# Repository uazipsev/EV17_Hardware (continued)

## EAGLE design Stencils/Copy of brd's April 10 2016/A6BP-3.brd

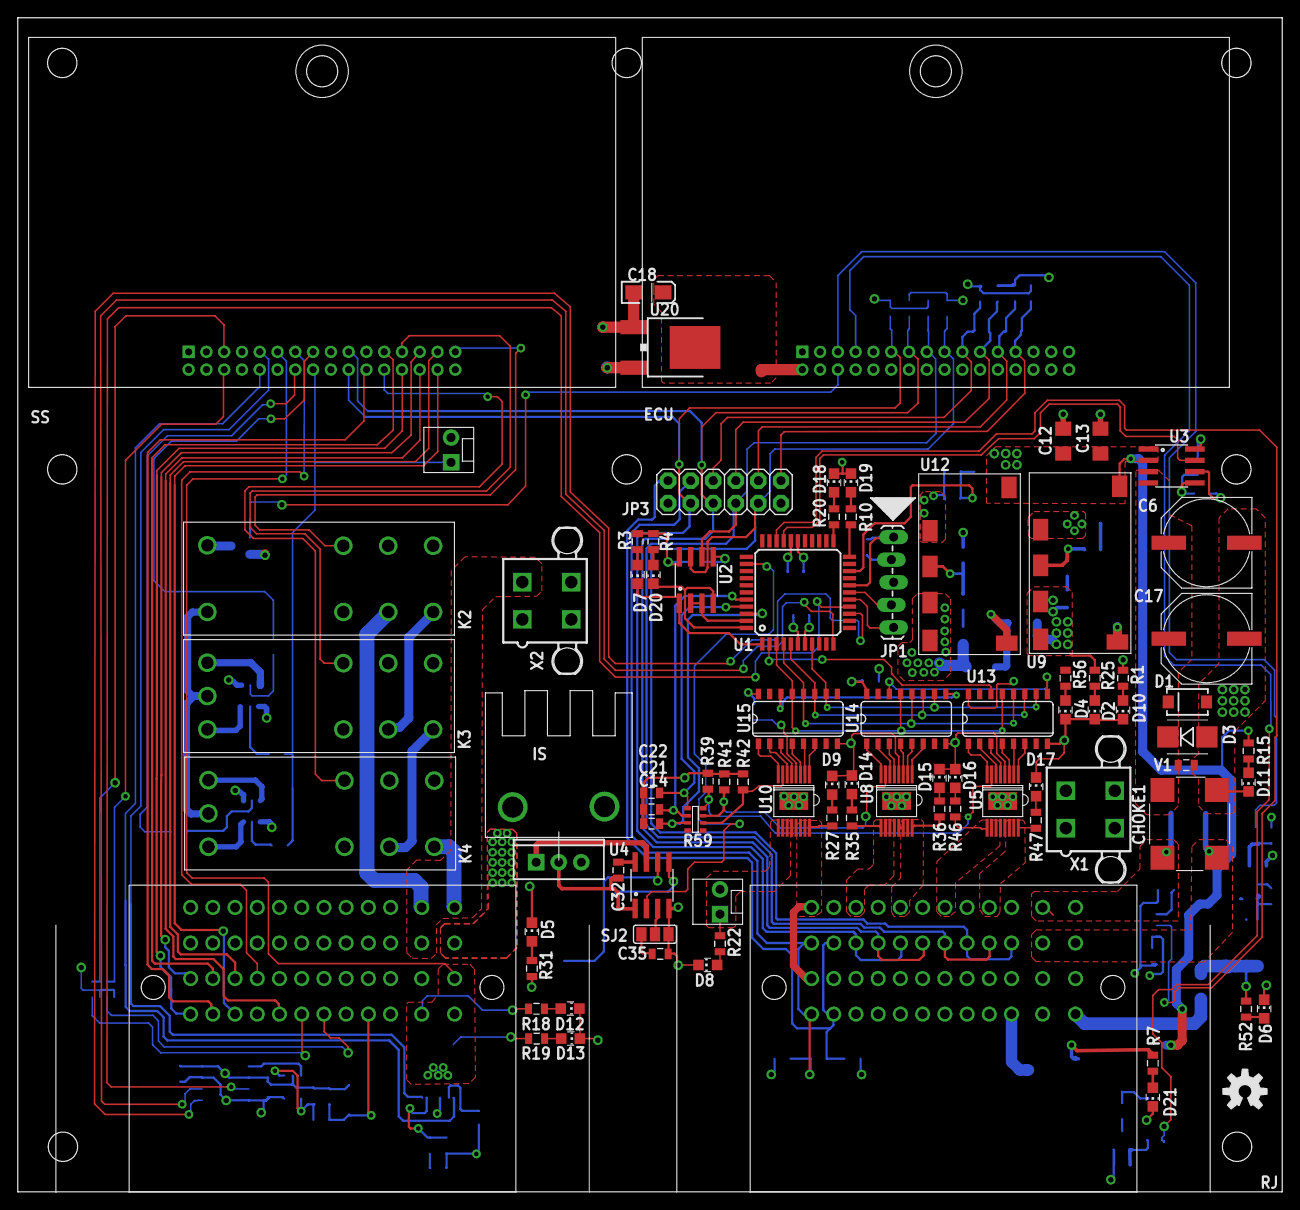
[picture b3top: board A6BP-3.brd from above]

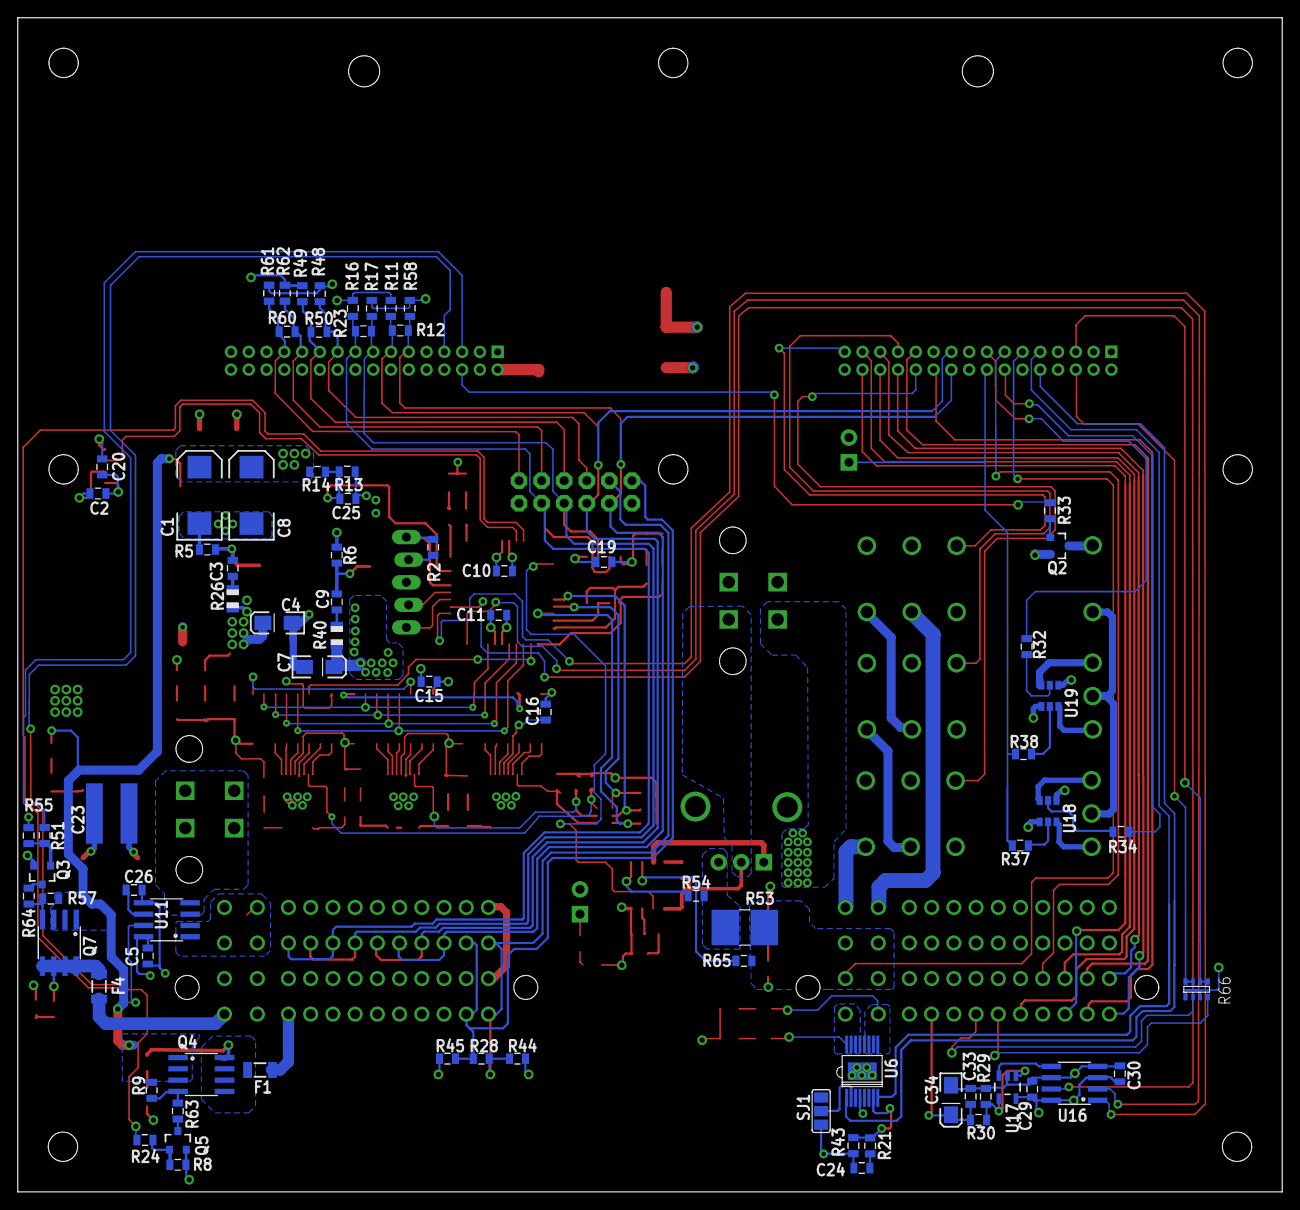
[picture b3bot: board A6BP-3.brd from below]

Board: 4 copper layers, 142.2 x 132.1 mm, 174 parts (79 on the bottom side), 163 nets.

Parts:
C1, C8: 10UF; EIA7343
C2, C5, C10, C11, C14, C15, C16, C19, C20, C21, C22, C24, C26: 0.1UF; 0805
C3, C9, C35: DNP; 0805
C4, C7, C18: 10UF; EIA3216-16V
C6, C17: 100UF_50V; PANASONIC-G
C12, C13: 1UF; 1206@1
C23: 1000PF; C1825
C25: 1UF; 0805
C29, C30, C33: 0.1uF; 0805
C32: CAP_2.7NF_50V; 0805
C34: 10UF_16V; EIA3216-16V
CHOKE1: 744272471
D1: 33.3V; SMA
D2, D4, D5, D6, D7, D8, D9, D10, D11, D12, D13, D14, D15, D16, D17, D18, D21: GREEN; CHIP_LED0805
D3: 33V; SMB
D19, D20: RED; CHIP_LED0805
ECU: CARD-2016RECP; CARD-2016-RCP
F1, F4: PTCSMD; PTC-1206
HS1: HEATSINK; 581002B02500G
J1, J2: 36638
J3, J4: M2M1X2; MOLEX-1X2
JP1: 1X05_LOCK_LONGPADS
JP3: 2X6 FEMALE; 2X6
K2: RTE44024F
K3, K4: RT424F24
Q1: IRLZ44; TO-220
Q2: NUD3160LT1G; SOT23
Q3, Q5: BSS123; SOT23
Q4, Q7: Si9435BDY; SO08
R1, R3, R4, R10, R18, R19, R20, R21, R24, R30, R32, R33, R34, R37, R38, R39, R41, R42, R51: 1K; 0805
R2, R8, R9, R43, R55, R57: 10K; 0805
R5: 8.45K; 0805
R6: 16.2K; 0805
R7, R31, R52: 3.3K; 0805
R11, R16, R17, R44, R45, R48, R49, R58, R61, R62: 620; 0805
R12, R23, R28, R50, R60: 120; 0805
R13: 24K; 0805
R14: \95.3K; 0805
R15: 3.3k; 0805
R22, R27, R35, R36, R46, R47: 1.21K; 0805
R25, R56: 1.2K; 0805
R26, R40: dnp; R0805
R29: 100K; 0805
R53: 0.003_3W; 2512
R54: 1k_1%; 0805
R59: 10K; MNR14
R63, R64: 6.04K; 0805
R65: 330_1%; 0805
R66: 100K; MNR14
SJ1, SJ2: PAD-JUMPER-3-NO_YES_SILK_FULL_BOX
SS: CARD-2016RECP; CARD-2016-RCP
STANDOFF1, STANDOFF2, STANDOFF3, STANDOFF4, STANDOFF5, STANDOFF6, STANDOFF7, STANDOFF8: STAND-OFF
U1: PIC18F45K22; TQFP-44
U2: SN75HVD08DRSOIC; SO-8
U3: ACS712-5A; SO-8
U4: MIC5021; SO-8
U5, U6, U8, U10: VND7040AJTR-E; SSO-16-POWER
U9, U12: APXW003A0X3-SRZ
U11: ACS712-30A; SO-8
U13, U14, U15: SN74LV594ADR; SO-16
U16: X9015_DIGI_POTS; SO08
U17: OPA344; SOT23-5
U18, U19: NUD3160DMT1G; SC74-6
U20: NCP1117DT_3.3; DPAK
U$8: OSHW-LOGOM; OSHW-LOGO-M
U$9: INDPK1; PICKIT-PIN-1
V1: 35V; 0805
X1, X2: 5566-4

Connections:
1AVAL: C22.1, R59.1, U1.41
2AVAL: C21.1, R59.2, U1.40
3AVAL: C14.1, R59.3, U1.42
!CS: U1.15, U16.7
+3V3: C18.A, ECU.2, U20.2
+5V: C5.1, C7.A, C10.1, C11.1, C15.1, C16.1, C19.1, C20.1, C29.1, C30.1, J4.2, JP1.2, JP3.1, R1.2, R2.2, R3.2, R4.2, R17.2, R40.1, R44.2, R48.2, R58.2, R61.2, SS.1, U1.7, U1.28, U2.8, U3.8, U11.8, U12.5, U12.6, U13.16, U14.16, U15.16, U16.3, U16.8, U17.5, U20.3
+24V: C1.A, C8.A, C12.1, C13.1, K2.A1, K3.A3, K4.A3, Q4.1, Q4.2, Q4.3, Q7.1, Q7.2, Q7.3, R9.2, R14.2, R15.2, R57.2, U3.1, U3.2, U9.2, U12.2
AIR-BOT+PRE: J1.48, R19.2, U6.13, U6.14, U6.15, U6.16
AIR-P: J1.42, X2.2
AIR-TOP: J1.44, R18.2, U6.9, U6.10, U6.11, U6.12
AMD-SEN: J1.11, SS.29
B-LIGHT: F4.1, J2.48
B-LIGHT-C: ECU.5, R51.1
BMS-P: J2.25, R46.2, U5.9, U5.10, U5.11, U5.12
BOTS-SEN: J1.12, SS.30
BPD-R-SET: R34.1, SS.14
BPD-SEN: K4.22, SS.24
BRAKE_PRESURE: R66.1, R66.2, SS.5
CLEAR: U1.8, U13.10, U14.10, U15.10
CLK: U1.5, U13.11, U14.11, U15.11
CSENSE: U1.30, U3.7
CURRENT_SENSOR: R66.3, R66.4, SS.6
DATA-IN: U1.2, U13.14
DDS-P: J2.17, R36.2, U8.13, U8.14, U8.15, U8.16
ECU-RELAY: ECU.6, R33.1
ECU-SEN: K2.22, SS.31
FAN: C32.1, Q1.2, U4.1, X2.3
FAN-PWM: U1.35, U4.2
FANMOTOR: J1.43, R31.2, R53.1, R65.2
FROM-TSMS: J1.47, SS.11, U6.EP
GND: C1.C, C2.2, C4.C, C5.2, C6.-, C7.C, C8.C, C10.2, C11.2, C12.2, C13.2, C14.2, C15.2, C16.2, C17.-, C18.C, C19.2, C20.2, C21.2, C22.2, C24.2, C25.2, C26.2, C29.2, C30.2, C33.2, C34.C, C35.2, CHOKE1.2, D1.A, D2.C, D3.A, D4.C, D5.C, D6.C, D8.C, D9.C, D10.C, D11.C, D12.C, D13.C, D14.C, D15.C, D16.C, D17.C, D18.C, D19.C, D21.C, ECU.32, J2.5, J2.7, J2.13, J2.21, J2.29, J2.36, J2.37, J2.44, JP1.3, JP3.11, K2.21, K3.21, K4.21, Q2.2, Q3.2, Q5.2, R5.1, R6.1, R8.1, R11.1, R13.1, R16.1, R29.1, R39.1, R41.1, R42.1, R43.1, R45.1, R49.1, R55.1, R62.1, R66.5, R66.7, SJ1.3, SJ2.1, SS.32, U1.6, U1.29, U2.5, U3.5, U4.4, U5.4, U6.4, U8.4, U9.1, U9.3, U10.4, U11.5, U12.1, U12.3, U13.8, U14.8, U15.8, U16.4, U16.6, U17.2, U18.1, U18.4, U19.1, U19.4, U20.1, V1.1
H-SIG: ECU.7, R24.1
HCMESURE: U1.31, U11.7
HORN+: F1.1, J2.40
IMD-INPUT: J1.15, SS.13
IMD-R-SET: R32.1, SS.15
IMD-SEN: K3.22, SS.25
INC: U1.14, U16.1
IS-SEN: J1.7, SS.23
LAT: U1.4, U13.12, U14.12, U15.12
LED1: R10.2, U1.22
LED2: R20.1, U1.23
LOOP-IN: J1.41, K2.11
MAIN: SS.9, U6.8
MCS-P: J2.33, R47.2, U5.13, U5.14, U5.15, U5.16
unnamed: D2.A, R25.1
unnamed: D12.A, R18.1
unnamed: D4.A, R56.1
unnamed: U5.8, U13.1
unnamed: Q4.4, R9.1, R63.2
unnamed: R34.2, U18.2
unnamed: K2.14, K3.11
unnamed: D10.A, R1.1
unnamed: F1.2, Q4.5, Q4.6, Q4.7, Q4.8, R7.2
unnamed: D13.A, R19.1
unnamed: R21.2, R43.2, U6.7
unnamed: D21.A, R7.1
unnamed: F4.2, Q7.5, Q7.6, Q7.7, Q7.8, R52.2
unnamed: SJ1.2, U6.2
unnamed: K3.14, K4.11
unnamed: D19.A, R10.1
unnamed: J3.1, J3.2, R22.2, U10.9, U10.10, U10.11, U10.12
unnamed: C2.1, U3.6
unnamed: Q2.1, R33.2
unnamed: U16.5, U17.3
unnamed: Q1.1, U4.7
unnamed: D5.A, R31.1
unnamed: R38.1, U19.5
unnamed: D7.A, R3.1
unnamed: D20.A, R4.1
unnamed: SJ2.2, U4.3
unnamed: Q1.3, R53.2, R54.2
unnamed: D8.A, R22.1
unnamed: D9.A, R27.1
unnamed: C6.+, C17.+, CHOKE1.3, D1.C, D3.C, U3.3, U3.4, V1.2
unnamed: R42.2, R59.6, U10.7
unnamed: Q7.4, R57.1, R64.2
unnamed: U5.6, U13.2
unnamed: D6.A, R52.1
unnamed: C3.1, R26.2
unnamed: U5.5, U13.3
unnamed: C3.2, R5.2, U9.4
unnamed: R54.1, U4.5
unnamed: U5.3, U13.4
unnamed: JP1.4, U1.17
unnamed: Q5.1, R8.2, R24.2
unnamed: D11.A, R15.1
unnamed: JP1.5, U1.16
unnamed: U5.2, U13.5
unnamed: K2.A2, Q2.3
unnamed: JP1.1, R2.1, U1.18
unnamed: K3.A1, U19.6
unnamed: R32.2, U19.2
unnamed: K3.A2, U19.3
unnamed: K4.A1, U18.6
unnamed: K4.A2, U18.3
unnamed: Q5.3, R63.1
unnamed: Q3.3, R64.1
unnamed: D18.A, R20.2
unnamed: R37.1, U18.5
unnamed: R65.1, U4.6
unnamed: J1.24, R66.8
unnamed: U13.9, U14.14
unnamed: C9.1, R40.2
unnamed: C9.2, R6.2, U12.4
unnamed: U11.3, U11.4, X1.1, X1.2, X1.3, X1.4
unnamed: U5.1, U13.6
unnamed: C26.1, U11.6
unnamed: U8.8, U14.1
unnamed: U8.6, U14.2
unnamed: U8.5, U14.3
unnamed: D14.A, R35.1
unnamed: D15.A, R36.1
unnamed: R39.2, R59.8, U5.7
unnamed: U8.3, U14.4
unnamed: U8.2, U14.5
unnamed: U8.1, U14.6
unnamed: U10.8, U15.1
unnamed: U10.6, U15.2
unnamed: U10.5, U15.3
unnamed: U10.3, U15.4
unnamed: U10.2, U15.5
unnamed: U10.1, U15.6
unnamed: D16.A, R46.1
unnamed: U14.9, U15.14
unnamed: C32.2, U4.8
unnamed: C35.1, SJ2.3
unnamed: D17.A, R47.1
unnamed: Q3.1, R51.2, R55.2
unnamed: R41.2, R59.7, U8.7
unnamed: J1.28, R66.6
OUTEN: U1.3, U13.13, U14.13, U15.13
PRE+: SS.10, U6.1
PUMP: J1.46, X2.1
PUMP_CONTROL_OUT: C33.1, C34.A, J1.36, R30.2
PUMP_OUTPUT_CONTROL: R29.2, R30.1, U17.1, U17.4
RAVAL: C24.1, R21.1
RELAY-SET: J4.1, R37.2, R38.2, SS.16
RS1-A: ECU.11, J2.10, J2.18, JP3.3, R12.2, R58.1, SS.20
RS1-B: ECU.13, J2.14, J2.22, JP3.5, R11.2, R12.1, SS.19
RS2-A: ECU.15, J2.26, J2.34, JP3.7, R17.1, R23.2, U2.6
RS2-B: ECU.17, J2.30, J2.38, JP3.9, R16.2, R23.1, U2.7
RX: D7.C, U1.1, U2.1
SAS-P: J2.9, R35.2, U8.9, U8.10, U8.11, U8.12
SSW_C_SEN: J1.4, SS.26
SSW_L-SEN: J1.20, SS.28
SSW_R-SEN: J1.3, SS.27
TM-A: ECU.25, JP3.12, R60.2, R61.1
TM-B: ECU.23, JP3.10, R60.1, R62.2
TM-Y: ECU.19, JP3.6, R48.1, R50.2
TM-Z: ECU.21, JP3.8, R49.2, R50.1
TO-TSMS: J1.45, K4.14
TSA: J2.2, J2.4, JP3.4, R28.2, R44.1
TSB: J2.6, J2.8, JP3.2, R28.1, R45.2
TSMS-SEN: J1.8, SS.22
TSS-P: J2.1, J2.3, R27.2, U10.13, U10.14, U10.15, U10.16
TX: D20.C, U1.44, U2.4
U2-CNT: U1.43, U2.2, U2.3
UP/!DN: U1.11, U16.2
VCCIO: C4.A, R25.2, R26.1, U5.EP, U8.EP, U9.5, U9.6, U10.EP
VGND: C23.2, CHOKE1.1, J2.42, J2.46
VIN: C23.1, CHOKE1.4, J2.41, J2.45, U11.1, U11.2
VSENSE: C25.1, R13.2, R14.1, U1.20

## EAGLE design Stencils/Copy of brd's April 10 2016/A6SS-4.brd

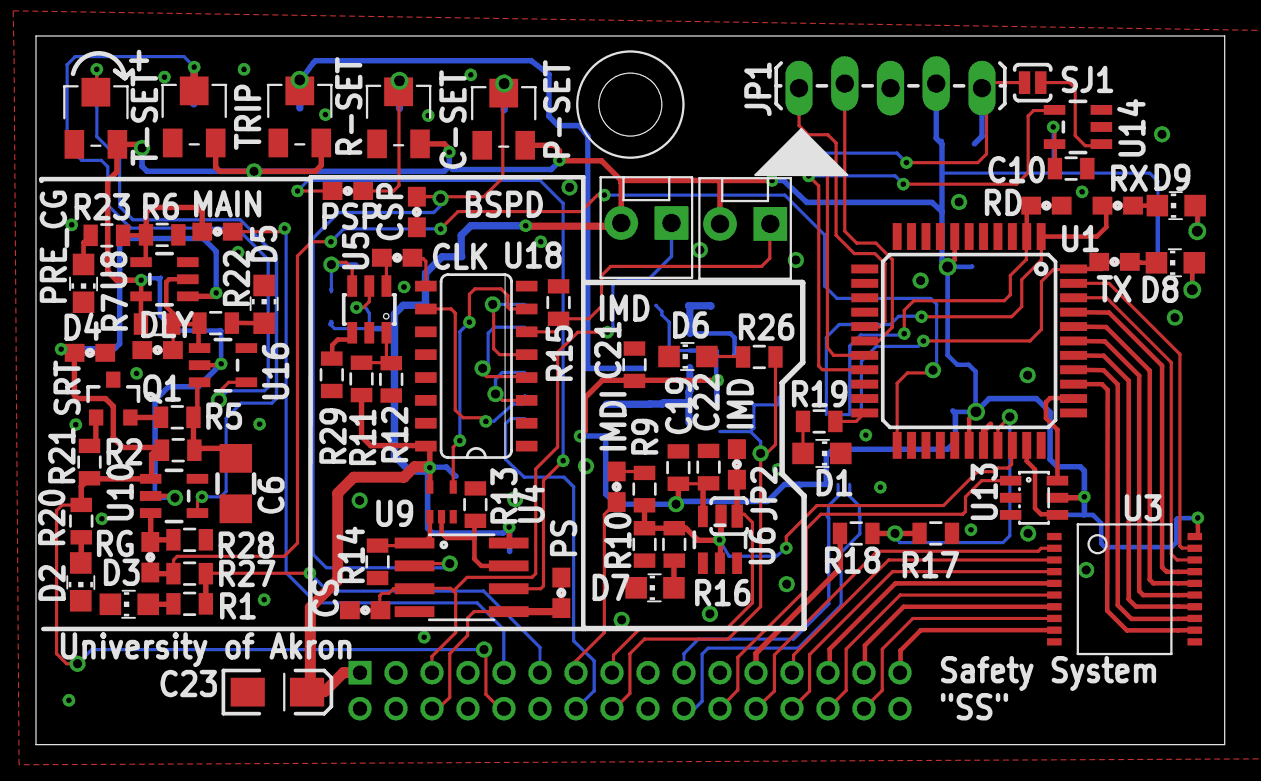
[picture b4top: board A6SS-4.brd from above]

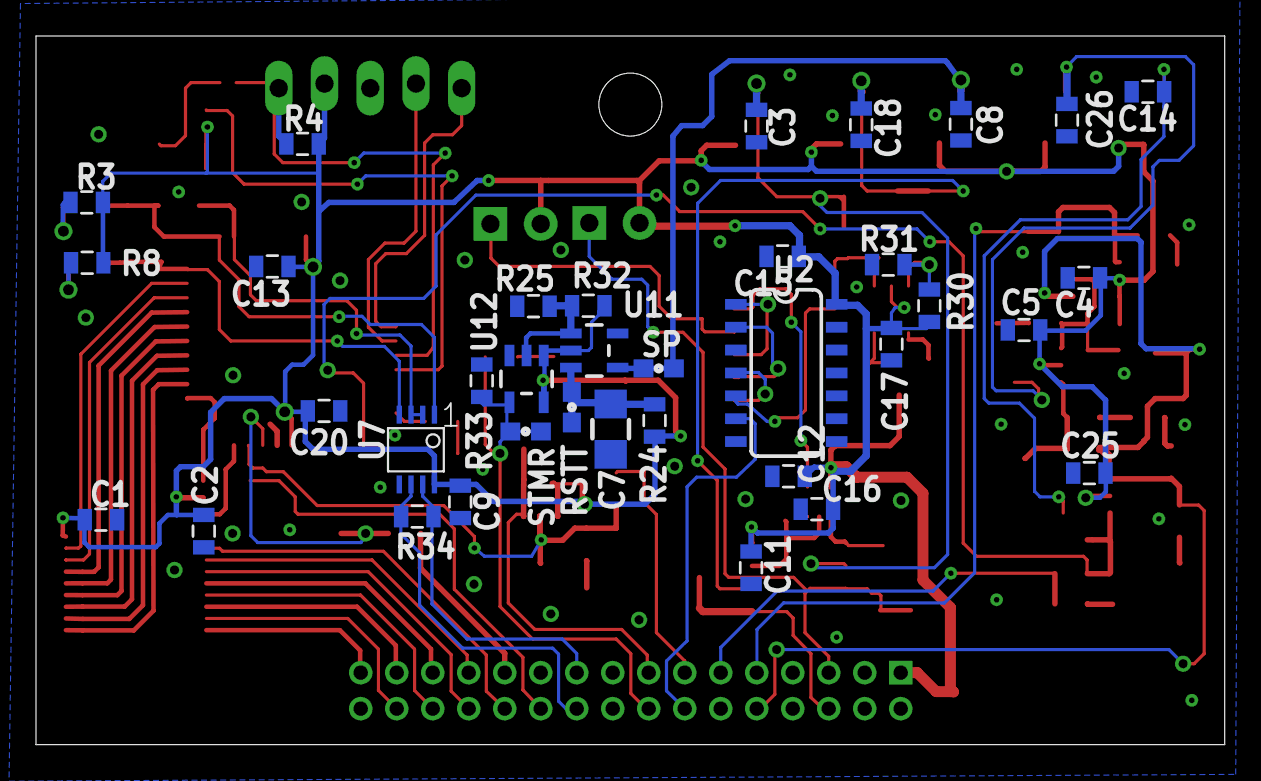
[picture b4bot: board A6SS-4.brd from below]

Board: 2 copper layers, 66.0 x 39.4 mm, 114 parts (36 on the bottom side), 77 nets.

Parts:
C1, C2, C4, C5, C9, C10, C11, C12, C13, C15, C16, C17, C19, C20, C21, C22, C25: 0.1UF; 0805
C3, C8, C14, C18, C26: 1UF; 0805
C6, C7: 100UF; 1206
C23: 10UF; EIA3216-16V
CARD1: CARD-2016CARD; CARD-2016
CLK: TP; 0603
CS: TP; 0603
CSP: TP; 0603
D1: AMBER; CHIP_LED0805
D2, D3, D4, D5, D6, D7, D8: GREEN; CHIP_LED0805
D9: RED; CHIP_LED0805
DLY: TP; 0603
IMD: TP; 0603
IMDI: TP; 0603
J1, J2: M2M1X2; MOLEX-1X2
JP1: 1X05_LOCK_LONGPADS
JP2: SJ_2S-NO
MAIN: TP; 0603
POT1, POT2, POT3, POT4, POT5: 22AR100KLFTR
PS: TP; 0603
PSP: TP; 0603
Q1: MMBT4403LT3G; SOT23
R1: 2.2K; 0805
R2, R24: 115K; 0805
R3, R8, R19, R20, R21, R22, R23, R26: 1K; 0805
R4, R13, R14, R15: 10K; 0805
R5: 5; 0805
R6, R7, R25, R32, R33: 2.7K; 0805
R9, R18: 28K; 0805
R10, R17, R28: 5K; 0805
R11, R12, R16: 1k; 0805
R27: 28k; 0805
R29: 91K; 0805
R30: 976K; 0805
R31: 182K; 0805
R34: 120; 0805
RD: TP; 0603
RG: TP; 0603
RSTT: TP; 0603
RX: TP; 0603
SJ1: SJ_2S-NO
SP: TP; 0603
SRT: TP; 0603
STMR: TP; 0603
TX: TP; 0603
U1: PIC18F45K22; TQFP-44
U2: SN74HC21DR; SO-14
U3: MAX6818; SSOP-20
U4: LM358PSR; SO-8
U5: LTC6991; TSOT-23-6
U6: NC7S14M5X; SOT23-5
U7: SN75HVD08DRMSOP; MSOP-8
U8: SN74AHC1G08DBVR; SOT23-5
U9: NC7SZ08P5X; SC-70-5
U10, U11, U16: MCP6541RT-E/OT; SOT23-5
U12: SN74LVC1G132DBVR; SOT23-5
U13: MAX6817EUT+T; SOT23-6
U14: MAX823TEUK+T_3.08; SOT23-5
U18: CD4015BM96; SO-16
U$1: INDPK1; PICKIT-PIN-1

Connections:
+5V: C1.1, C2.1, C4.1, C5.1, C9.1, C10.1, C11.1, C12.1, C13.1, C15.1, C16.1, C17.1, C19.1, C20.1, C21.1, C22.1, C23.A, C25.1, CARD1.1, J1.2, J2.2, JP1.2, POT1.1, POT2.1, POT3.1, POT4.1, POT5.1, R3.2, R4.2, R7.2, R8.2, R11.2, R24.1, R30.2, R32.2, U1.7, U1.28, U2.14, U3.20, U4.8, U5.5, U6.5, U7.8, U8.5, U9.5, U10.2, U11.2, U12.1, U12.5, U13.5, U14.5, U16.2, U18.16
AMD: CARD1.29, U3.7
AMD_O: U1.41, U3.17
AUX_O: U1.32, U13.4
BOTS: CARD1.30, U3.8
BOTS_O: U1.42, U3.18
BPD: CARD1.24, U3.2
BPD-R-SET: CARD1.14, U2.6
BPD_O: U1.36, U3.12
BRAKE_PRESURE: CARD1.6, PS.1, PS.2, U4.5
CURRENT_SENSOR: CARD1.5, CS.1, CS.2, J2.1, U4.3
ECU: CARD1.31, U3.9
ECU_O: U1.43, U3.19
GND: C1.2, C2.2, C3.2, C4.2, C5.2, C6.2, C7.2, C8.2, C9.2, C10.2, C11.2, C12.2, C13.2, C14.2, C15.2, C16.2, C17.2, C18.2, C19.2, C20.2, C21.2, C22.2, C23.C, C25.2, C26.2, CARD1.32, D1.C, D2.C, D3.C, D4.C, D5.C, D6.C, D7.C, JP1.3, POT1.3, POT2.3, POT3.3, POT4.3, POT5.3, Q1.3, R6.1, R10.1, R12.1, R13.1, R14.1, R15.2, R17.1, R25.1, R28.1, R29.1, R31.1, R33.1, U1.6, U1.29, U2.7, U3.1, U3.10, U4.4, U5.2, U6.3, U7.5, U8.3, U9.3, U10.5, U11.5, U12.3, U13.2, U14.2, U16.5, U18.8
IMD: CARD1.25, U3.3
IMD-R-SET: CARD1.15, IMD.1, IMD.2, JP2.1, U6.4
IMD-SIG: CARD1.13, IMDI.1, IMDI.2, R9.2
IMD_O: U1.37, U3.13
IMD_STAT: JP2.2, R9.1, R10.2, R16.2, U1.31, U6.2
IS_O: R17.2, R18.1, U1.30
MAIN: CARD1.9, MAIN.1, MAIN.2, R6.2, R23.1, U8.4
unnamed: SJ1.1, U14.1
unnamed: CARD1.23, R18.2
unnamed: C26.1, POT2.2, U16.4
unnamed: C8.1, POT5.2, SP.1, SP.2, U11.4
unnamed: Q1.1, R21.1
unnamed: Q1.2, R5.1
unnamed: U2.5, U18.10
unnamed: D9.A, R3.1
unnamed: D8.A, R8.1
unnamed: R30.1, R31.2, U5.4
unnamed: C14.1, POT1.2, U10.4
unnamed: D7.A, R16.1
unnamed: U9.4, U18.7
unnamed: J1.1, R15.1, U18.6
unnamed: C7.1, R24.2, RSTT.1, RSTT.2, U11.3
unnamed: D1.A, R19.1
unnamed: U2.1, U18.5
unnamed: U2.2, U18.4
unnamed: U2.4, U18.3
unnamed: R19.2, U1.22
unnamed: R29.2, U5.3
unnamed: CLK.1, CLK.2, U5.6, U18.9
unnamed: C3.1, CSP.1, CSP.2, POT4.2, U4.2
unnamed: R25.2, R32.1, U11.1, U12.2
unnamed: R11.1, R12.2, U5.1
unnamed: C18.1, POT3.2, PSP.1, PSP.2, U4.6
unnamed: D2.A, R20.1
unnamed: R14.2, U4.1, U9.1
unnamed: D6.A, R26.1
unnamed: R13.2, U4.7, U9.2
unnamed: D3.A, R1.1
unnamed: JP1.4, U1.17
unnamed: JP1.5, U1.16
unnamed: JP1.1, R4.1, SJ1.2, U1.18
unnamed: C6.1, R2.2, R5.2, U16.3
unnamed: DLY.1, DLY.2, R7.1, R22.1, U8.2, U16.1
unnamed: D4.A, R23.2
unnamed: D5.A, R22.2
RELAY-SET: CARD1.16, R26.2, R33.2, STMR.1, STMR.2, U12.4
RS-A: CARD1.20, R34.1, U7.6
RS-B: CARD1.19, R34.2, U7.7
RTG: CARD1.11, R1.2, R27.2
RTG_5V: R27.1, R28.2, RG.1, RG.2, U1.23, U10.3
RX1: D9.C, RX.1, RX.2, U1.1, U7.1
SSW_C: CARD1.26, U3.4
SSW_C_O: U1.38, U3.14
SSW_L: CARD1.28, U3.6
SSW_L_O: U1.40, U3.16
SSW_R: CARD1.27, U3.5
SSW_R_O: U1.39, U3.15
START: CARD1.10, R2.1, R20.2, R21.2, SRT.1, SRT.2, U8.1, U10.1
TSMS: CARD1.22, U13.1
TSMS_O: U1.35, U13.6
TX1: D8.C, TX.1, TX.2, U1.44, U7.4
U7-RE/DE: RD.1, RD.2, U1.2, U7.2, U7.3
WDT: U1.19, U14.4

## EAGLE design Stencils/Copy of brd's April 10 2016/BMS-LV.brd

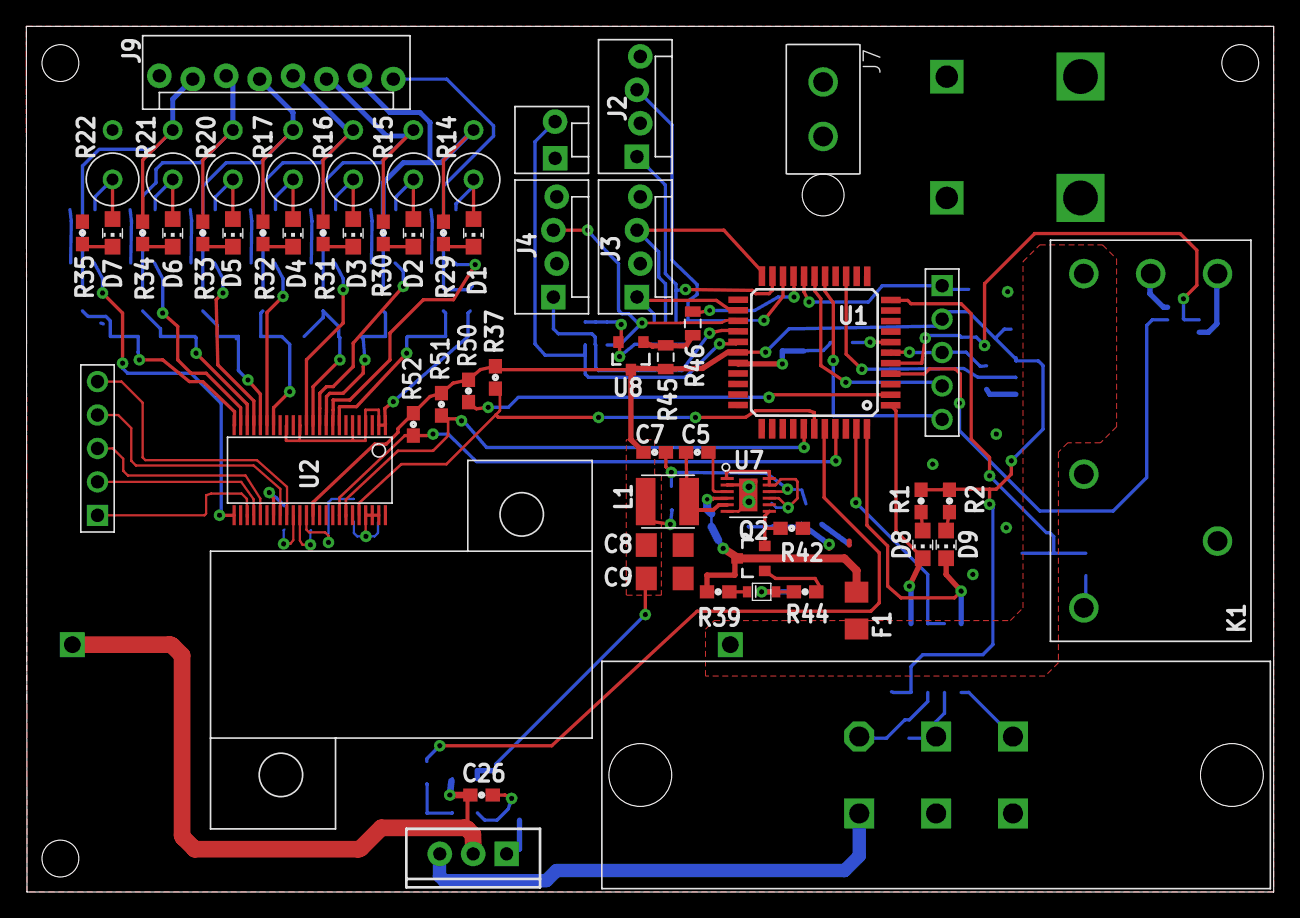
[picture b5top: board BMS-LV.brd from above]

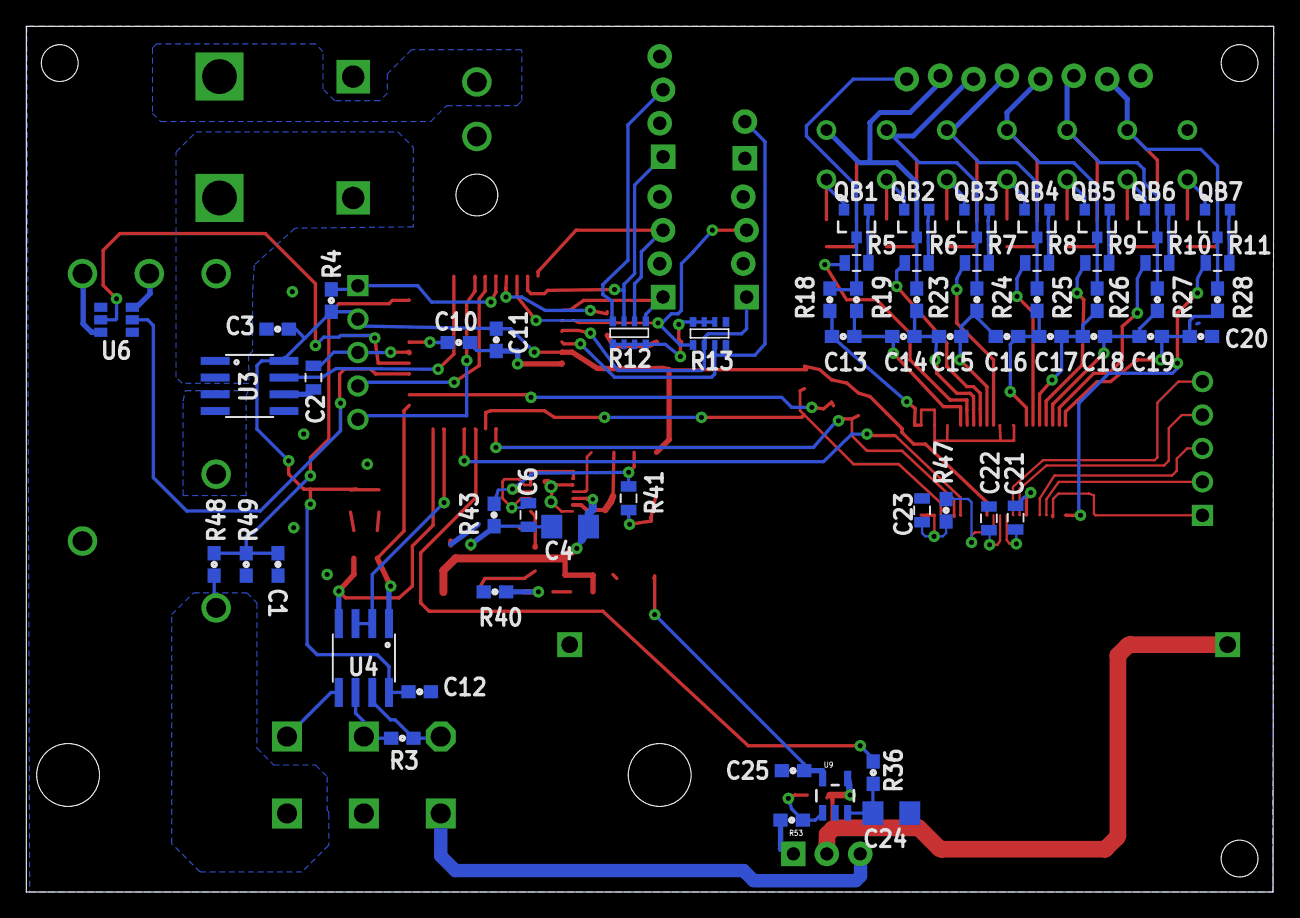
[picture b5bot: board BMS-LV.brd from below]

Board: 2 copper layers, 94.8 x 65.8 mm, 119 parts (59 on the bottom side), 106 nets.

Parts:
C1, C3, C5, C10, C11, C12, C25, C26: 0.1uF; 0603
C2: 0.1uF; 0805
C4: 4.7uF; 1206@1
C6, C21, C22, C23: 1uF; 0805
C7: 100pF; 0603
C8, C9, C24: 10uF; 1206@1
C13, C14, C15, C16, C17, C18, C19, C20: 10nF; 0603
D1, D2, D3, D4, D5, D6, D7, D9: LED_GREEN; CHIP_LED0805
D8: LED_AMBER; CHIP_LED0805
D10: 22V; SOD-323
F1: 0.12A 48V PTC; 1206@1
F2: FUSE CLIPS; FUSECLIP-3550
J1, J8: M1x5; 5X.1
J2, J3, J4: M1x4; MOLEX_1X4
J5: M1x2; MOLEX-1X2
J6: MX150L; MOLEX-MX150L
J7: M2770166; 1-770166-0
J9: M80022232081-2; MOLEX-1X8-2
K1: ADJ14024
L1: SRN4018-220M; SRN4018
Q2: 40V 0.2A; SOT23
Q3: BDX34C; TO-220
QB1, QB2, QB3, QB4, QB5, QB6, QB7: MOS-P_DMP2305U-7; SOT23
R1, R2, R29, R30, R31, R32, R33, R34, R35, R36: 1k; 0603
R3: 120; 0603
R4, R39, R40, R44: 10k; 0603
R5, R6, R7, R8, R9, R10, R11: 3.3k; 0805
R12, R13: 10k; MNR14
R14, R15, R16, R17, R20, R21, R22: 16; RR02J16RTB
R18, R19, R23, R24, R25, R26, R27, R28, R53: 100; 0603
R37, R50, R51, R52: 4.99k; 0603
R38: 0.5; CHASSIS-MNT-RES-TE-HSA25
R41: 91k; 0805
R42: 47k; 0603
R43: 12.4k; 0603
R45: 100k; 0805
R46: 1k; 0805
R47: RES_0_1%; 0603
R48: 32.4k; 0603
R49: 5.36k; 0603
U1: PIC18F45K22; TQFP-44
U2: LTC6804-2; SSOP-48
U3: ACS712; SO-8
U4: SN75HVD08DRSOIC; SO-8
U6: NUD3160DMT1G; SC74-6
U7: ISL85415-FRZ-T7A; DFN-12
U8: BSS308PE; SOT23
U9: OPA344; SOT23-5

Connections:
+5V: C3.1, C7.1, C8.1, C9.1, C11.1, C12.1, C25.1, J1.2, L1.P$2, R1.2, R2.2, R4.2, R37.2, R41.2, R45.2, R50.2, R51.2, R52.2, U1.28, U2.37, U3.8, U4.8, U8.3, U9.5
+36V: J6.4, Q3.3
ASENSE: U1.14, U3.7
BATTFUSED: F1.1, F2.2, K1.C+, R38.1, U3.1, U3.2
BATTPACK+: J9.8, QB1.3, R18.2, R19.1
CHARGECTRL: R36.1, U1.40
CLK: R51.1, U1.38, U2.42
CS: R52.1, U1.41, U2.41
GND: C1.2, C2.2, C3.2, C4.2, C6.2, C8.2, C9.2, C10.2, C11.2, C12.2, C20.2, C21.2, C22.2, C23.2, C24.2, C25.2, J1.3, J2.2, J2.4, J3.2, J3.4, J4.2, J4.4, J5.1, J6.5, J7.2, J9.1, R22.P$1, R35.1, R40.1, R42.1, R43.1, R49.1, U1.6, U1.29, U2.26, U2.30, U2.31, U2.40, U2.48, U3.5, U6.1, U6.4, U7.2, U7.6, U7.13, U9.2
GPIO1: J8.1, U2.27
GPIO2: J8.2, U2.28
GPIO3: J8.3, U2.29
GPIO4: J8.4, U2.32
GPIO5: J8.5, U2.33
I/O: J6.6, K1.C, R48.2
MISO: R37.1, U1.39, U2.44
MOSI: R50.1, U1.2, U2.43
unnamed: D8.A, R1.1
unnamed: C13.2, C14.1, R19.2, U2.8
unnamed: D9.A, R2.1
unnamed: C14.2, C15.1, R23.1, U2.10
unnamed: F2.1, J7.1
unnamed: J6.3, U4.5
unnamed: K1.-8-S, U6.6
unnamed: C15.2, C16.1, R24.1, U2.12
unnamed: J1.4, U1.17
unnamed: R45.1, R46.1, U8.1
unnamed: R47.1, U2.36
unnamed: D1.C, R29.2
unnamed: C24.1, R36.2, U9.3
unnamed: K1.NO, U3.3, U3.4
unnamed: C17.2, C18.1, R26.1, U2.20
unnamed: Q3.1, R53.2
unnamed: K1.-9-R, U6.3
unnamed: C26.1, R53.1, U9.1
unnamed: D2.C, R30.2
unnamed: C26.2, Q3.2, R38.2, U9.4
unnamed: C4.1, F1.2, Q2.3, R39.2, U7.4
unnamed: C2.1, U3.6
unnamed: D10.P$2, R40.2, R44.1
unnamed: J6.2, R3.1, U4.6
unnamed: D10.P$1, R39.1
unnamed: Q2.2, R42.2, U7.7
unnamed: C5.2, U7.3
unnamed: J6.1, R3.2, U4.7
unnamed: J9.2, QB7.3, R21.P$1, R28.2, R34.1
unnamed: C6.1, U7.1, U7.9, U7.11, U7.12
unnamed: C5.1, L1.P$1, U7.5
unnamed: C18.2, C19.1, R27.1, U2.22
unnamed: J1.5, U1.16
unnamed: C19.2, C20.1, R28.1, U2.24
unnamed: D3.C, R31.2
unnamed: Q2.1, R44.2
unnamed: D4.C, R32.2
unnamed: D5.C, R33.2
unnamed: QB5.1, R9.1
unnamed: D6.C, R34.2
unnamed: D5.A, QB5.2, R20.P$2
unnamed: QB3.1, R7.1
unnamed: J9.3, QB6.3, R20.P$1, R27.2, R33.1
unnamed: QB7.1, R11.1
unnamed: J9.4, QB5.3, R17.P$1, R26.2, R32.1
unnamed: D7.A, QB7.2, R22.P$2
unnamed: D7.C, R35.2
unnamed: QB6.1, R10.1
unnamed: J1.1, R4.1, U1.18
unnamed: D6.A, QB6.2, R21.P$2
unnamed: C7.2, R41.1, R43.2, U7.10
unnamed: J9.7, QB2.3, R14.P$1, R23.2, R29.1
unnamed: J9.6, QB3.3, R15.P$1, R24.2, R30.1
unnamed: J9.5, QB4.3, R16.P$1, R25.2, R31.1
unnamed: QB1.1, R5.1
unnamed: D1.A, QB1.2, R14.P$2
unnamed: QB2.1, R6.1
unnamed: D2.A, QB2.2, R15.P$2
unnamed: D3.A, QB3.2, R16.P$2
unnamed: QB4.1, R8.1
unnamed: D4.A, QB4.2, R17.P$2
unnamed: R12.5, R12.6, R12.7, R12.8, R13.6, R13.7, R13.8, U8.2
unnamed: C16.2, C17.1, R25.1, U2.18
RSET: U1.5, U6.5
RX1: D8.C, U1.1, U4.1
S1: R11.2, U2.25
S2: R10.2, U2.23
S3: R9.2, U2.21
S4: R8.2, U2.19
S7: R7.2, U2.13
S8: R6.2, U2.11
S9: R5.2, U2.9
SET: U1.4, U6.2
SHORT: C13.1, R18.1, U2.1, U2.2, U2.4, U2.6, U2.14, U2.16
TEMP1: J2.3, R12.4, U1.20
TEMP2: J2.1, R12.3, U1.21
TEMP3: J3.3, R12.2, U1.22
TEMP4: J3.1, R12.1, U1.24
TEMP5: J4.3, R13.1, U1.25
TEMP6: J4.1, R13.2, U1.26
TEMP7: J5.2, R13.3, U1.27
TFET: R46.2, U1.19
TX1: D9.C, U1.44, U4.4
U4: U1.43, U4.2, U4.3
VDD1: C10.1, U1.7
VEXTERNAL: C1.1, R48.1, R49.2, U1.11
VREF1: C22.1, U2.35
VREF2: C21.1, U2.34
VREG: C23.1, R47.2, U2.45, U2.46, U2.47
